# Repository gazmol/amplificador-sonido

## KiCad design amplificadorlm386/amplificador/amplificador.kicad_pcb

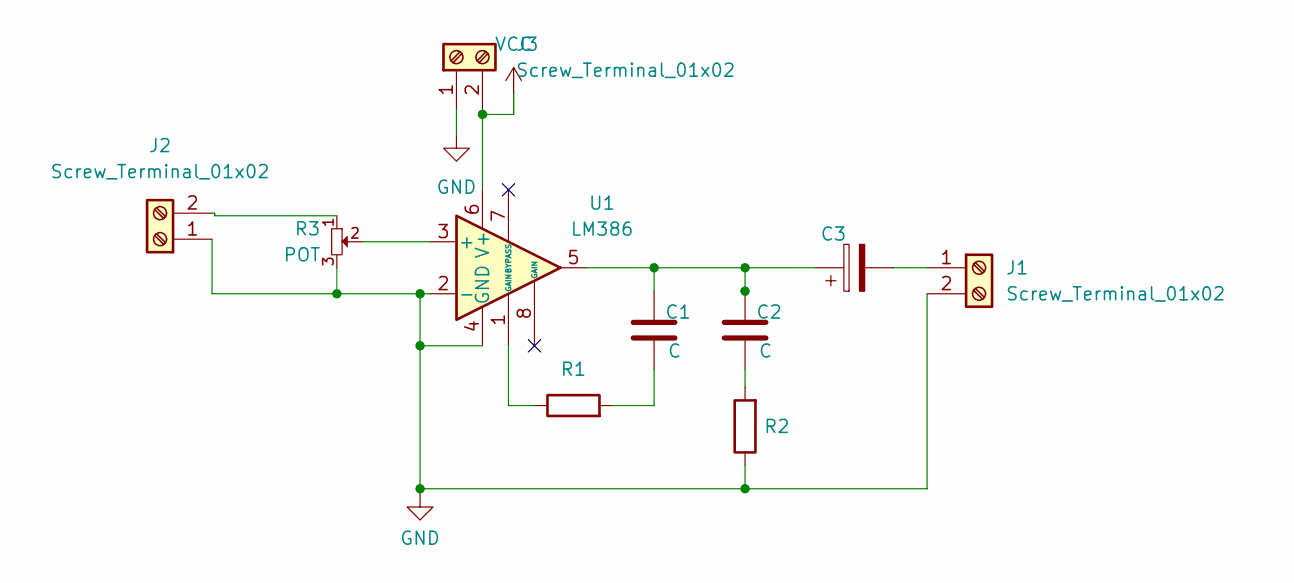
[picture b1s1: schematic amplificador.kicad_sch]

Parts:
C1, C2: C; C_Rect_L7.0mm_W2.5mm_P5.00mm
C3: C_Polarized; CP_Radial_D4.0mm_P2.00mm
J1, J2, J3: Screw_Terminal_01x02; TerminalBlock_bornier-2_P5.08mm
R1, R2: R; R_Axial_DIN0204_L3.6mm_D1.6mm_P5.08mm_Horizontal
R3: POT; Potentiometer_Alps_RK163_Single_Horizontal
U1: LM386; DIP-8_W7.62mm_LongPads

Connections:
GND: J1.2, J2.1, J3.1, R2.1, R3.3, U1.2 (-), U1.4 (GND)
unnamed: C1.1, C2.1, C3.1, U1.5
unnamed: C1.2, R1.2
unnamed: C2.2, R2.2
unnamed: C3.2, J1.1
unnamed: J2.2, R3.1
unnamed: R1.1, U1.1 (GAIN)
unnamed: R3.2, U1.3 (+)
VCC: J3.2, U1.6 (V+)

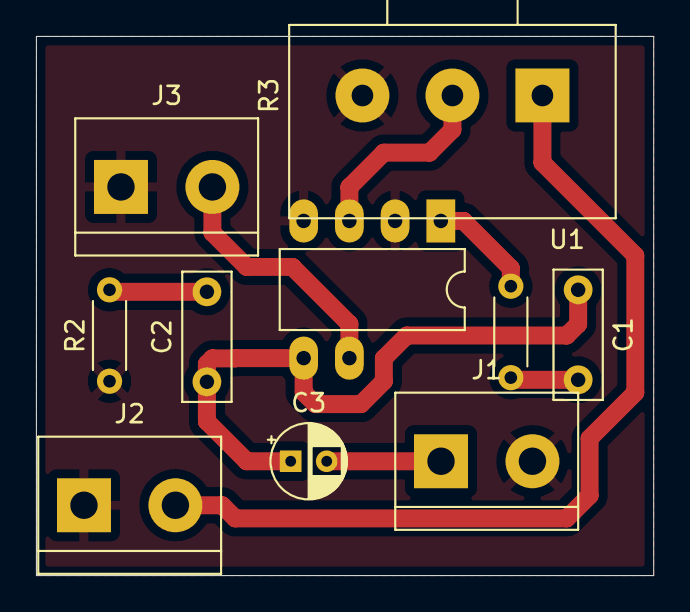
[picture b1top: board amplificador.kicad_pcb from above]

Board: 2 copper layers, 34.3 x 29.9 mm, 10 parts (0 on the bottom side), 9 nets.

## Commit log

2024-06-05 subí el archivo
